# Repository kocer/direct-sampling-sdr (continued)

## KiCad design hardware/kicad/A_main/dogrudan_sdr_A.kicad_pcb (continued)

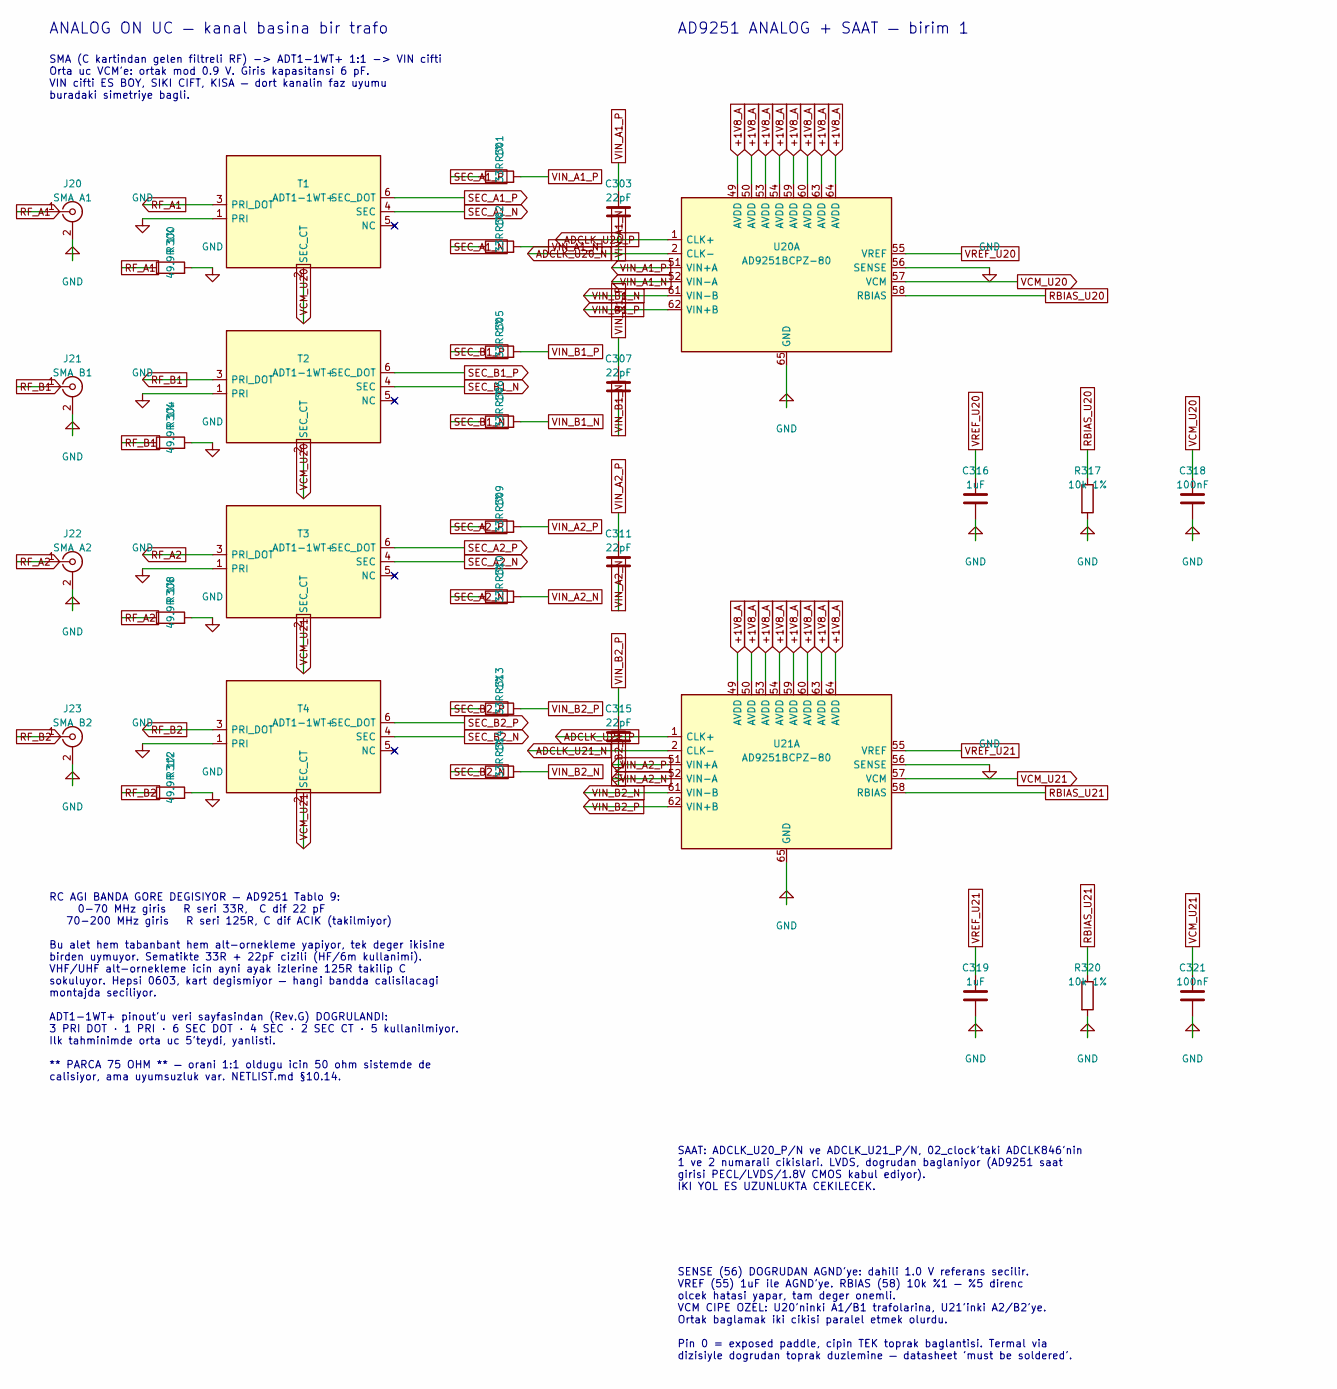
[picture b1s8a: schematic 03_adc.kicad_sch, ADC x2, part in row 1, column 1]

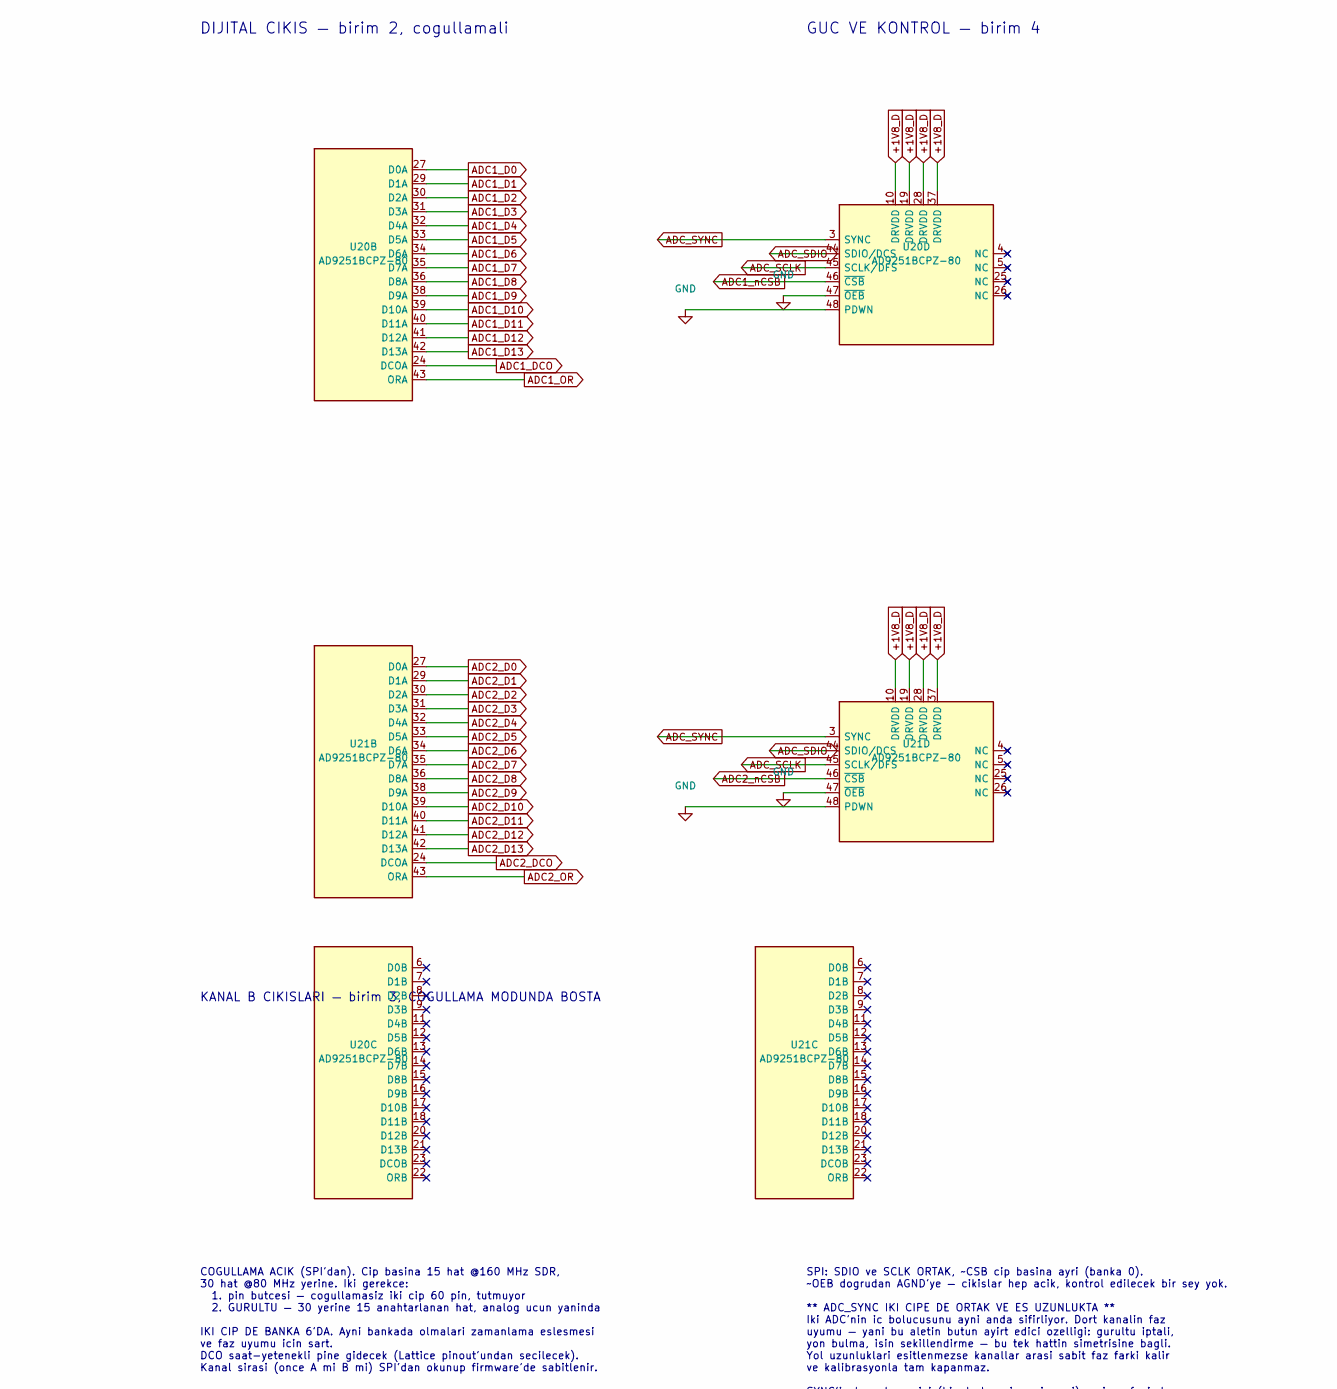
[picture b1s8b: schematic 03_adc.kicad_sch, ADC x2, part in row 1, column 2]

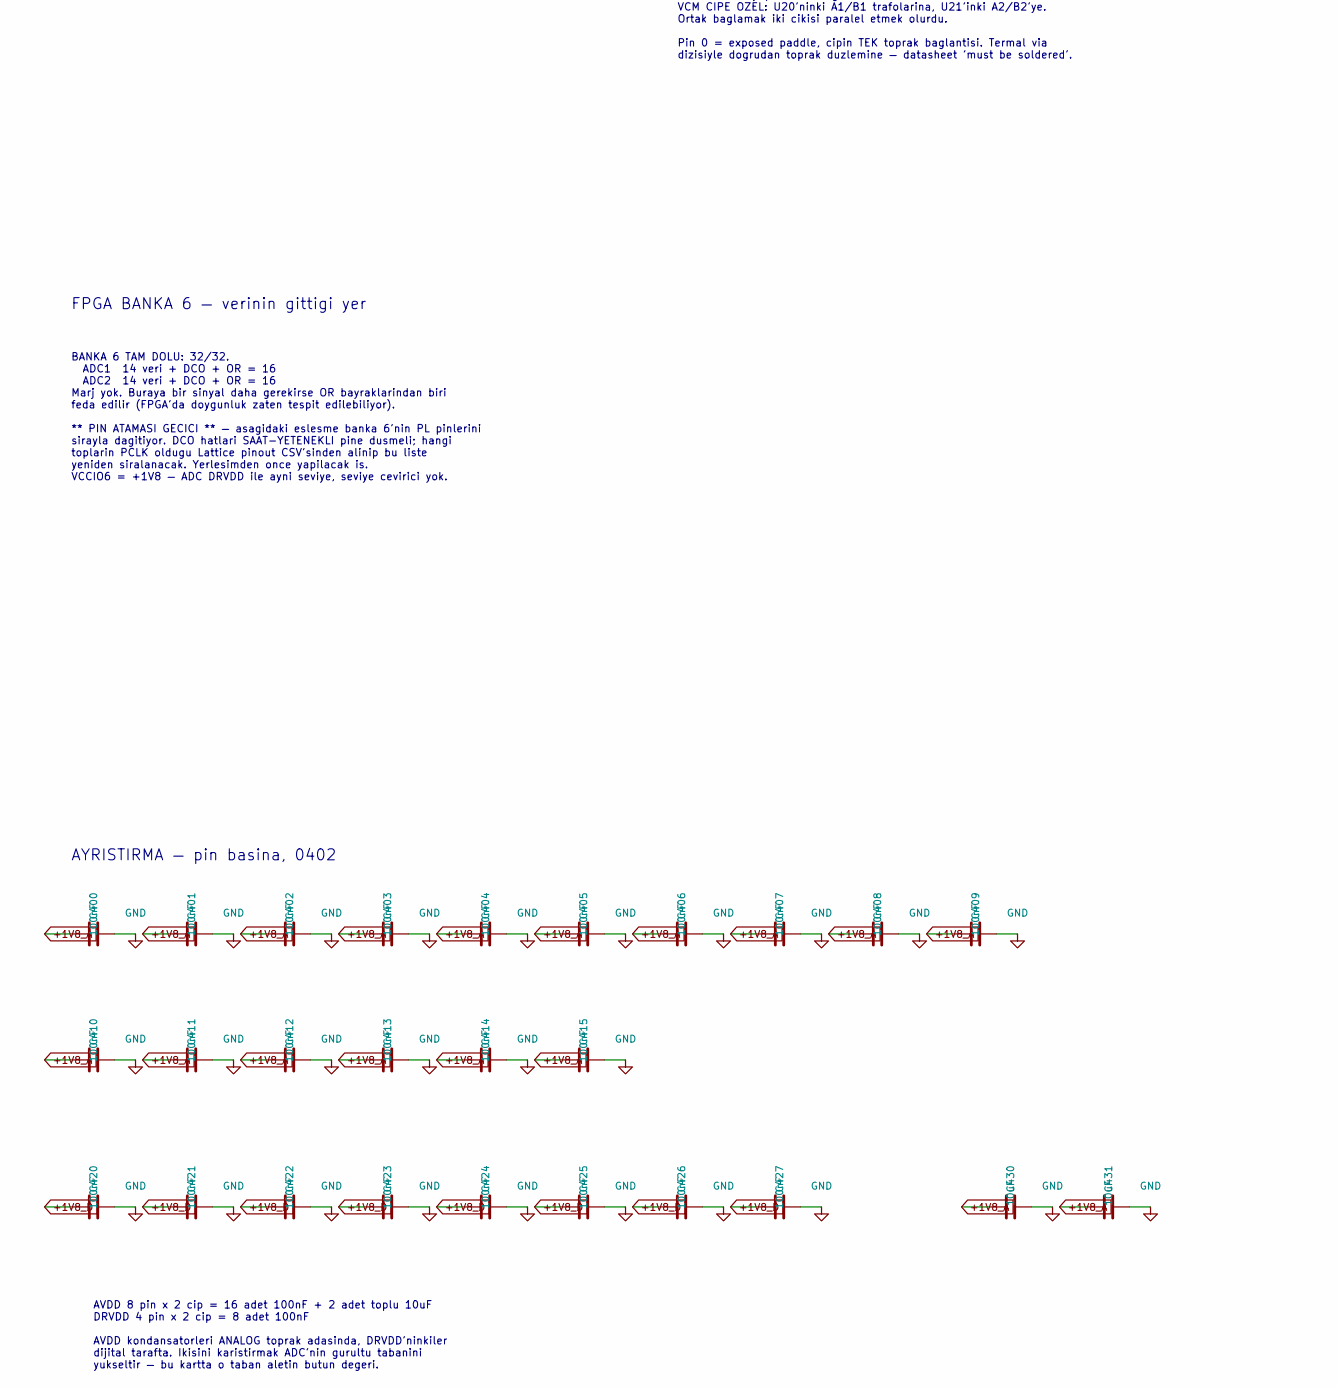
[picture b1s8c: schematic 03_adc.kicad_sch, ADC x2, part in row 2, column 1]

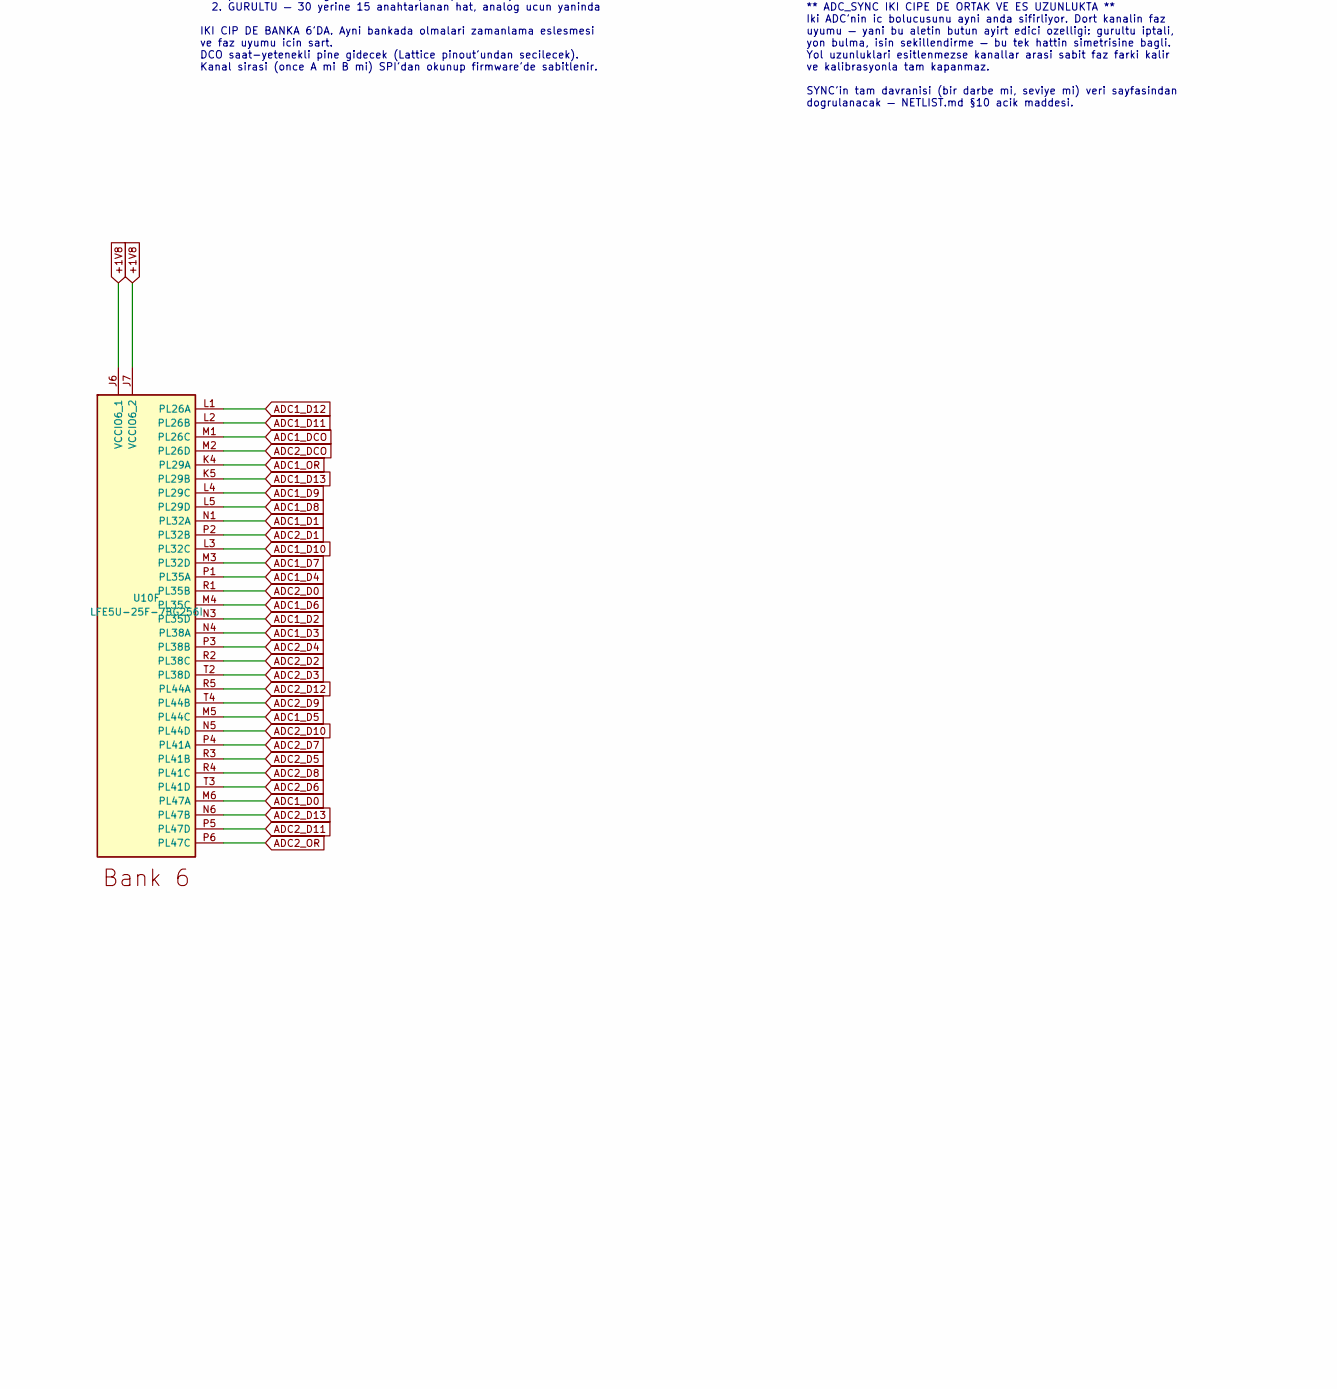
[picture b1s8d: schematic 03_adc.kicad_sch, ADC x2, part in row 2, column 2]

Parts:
C303, C307, C311, C315: 22pF; C_0603_1608Metric
C316, C319: 1uF; C_0603_1608Metric
C318, C321: 100nF; C_0603_1608Metric
C400, C401, C402, C403, C404, C405, C406, C407, C408, C409, C410, C411, C412, C413, C414, C415, C420, C421, C422, C423, C424, C425, C426, C427: 100nF; C_0402_1005Metric
C430, C431: 10uF; C_0402_1005Metric
J20: SMA A1; SMA_Amphenol_132289_EdgeMount
J21: SMA B1; SMA_Amphenol_132289_EdgeMount
J22: SMA A2; SMA_Amphenol_132289_EdgeMount
J23: SMA B2; SMA_Amphenol_132289_EdgeMount
R300, R304, R308, R312: 49.9R 1%; R_0603_1608Metric
R301, R302, R305, R306, R309, R310, R313, R314: 33R 1%; R_0603_1608Metric
R317, R320: 10k 1%; R_0603_1608Metric
T1, T2, T3, T4: ADT1-1WT+; Mini-Circuits_CD542_H2.84mm
U10: LFE5U-25F-7BG256I; BGA-256_14.0x14.0mm_Layout16x16_P0.8mm_Ball0.45mm_Pad0.32mm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
U20, U21: AD9251BCPZ-80; QFN-64-1EP_9x9mm_P0.5mm_EP4.7x4.7mm

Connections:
+1V8: U10.J6 (VCCIO6_1), U10.J7 (VCCIO6_2); also elsewhere on the board
+1V8_D: C420.1, C421.1, C422.1, C423.1, C424.1, C425.1, C426.1, C427.1, U20.10 (DRVDD), U20.19 (DRVDD), U20.28 (DRVDD), U20.37 (DRVDD), U21.10 (DRVDD), U21.19 (DRVDD), U21.28 (DRVDD), U21.37 (DRVDD); also elsewhere on the board
ADC1_D0: U10.M6 (PL47A), U20.27 (D0A)
ADC1_D1: U10.N1 (PL32A), U20.29 (D1A)
ADC1_D2: U10.N3 (PL35D), U20.30 (D2A)
ADC1_D3: U10.N4 (PL38A), U20.31 (D3A)
ADC1_D4: U10.P1 (PL35A), U20.32 (D4A)
ADC1_D5: U10.M5 (PL44C), U20.33 (D5A)
ADC1_D6: U10.M4 (PL35C), U20.34 (D6A)
ADC1_D7: U10.M3 (PL32D), U20.35 (D7A)
ADC1_D8: U10.L5 (PL29D), U20.36 (D8A)
ADC1_D9: U10.L4 (PL29C), U20.38 (D9A)
ADC1_D10: U10.L3 (PL32C), U20.39 (D10A)
ADC1_D11: U10.L2 (PL26B), U20.40 (D11A)
ADC1_D12: U10.L1 (PL26A), U20.41 (D12A)
ADC1_D13: U10.K5 (PL29B), U20.42 (D13A)
ADC1_DCO: U10.M1 (PL26C), U20.24 (DCOA)
ADC1_OR: U10.K4 (PL29A), U20.43 (ORA)
ADC1_nCSB: U20.46 (~CSB); also elsewhere on the board
ADC2_D0: U10.R1 (PL35B), U21.27 (D0A)
ADC2_D1: U10.P2 (PL32B), U21.29 (D1A)
ADC2_D2: U10.R2 (PL38C), U21.30 (D2A)
ADC2_D3: U10.T2 (PL38D), U21.31 (D3A)
ADC2_D4: U10.P3 (PL38B), U21.32 (D4A)
ADC2_D5: U10.R3 (PL41B), U21.33 (D5A)
ADC2_D6: U10.T3 (PL41D), U21.34 (D6A)
ADC2_D7: U10.P4 (PL41A), U21.35 (D7A)
ADC2_D8: U10.R4 (PL41C), U21.36 (D8A)
ADC2_D9: U10.T4 (PL44B), U21.38 (D9A)
ADC2_D10: U10.N5 (PL44D), U21.39 (D10A)
ADC2_D11: U10.P5 (PL47D), U21.40 (D11A)
ADC2_D12: U10.R5 (PL44A), U21.41 (D12A)
ADC2_D13: U10.N6 (PL47B), U21.42 (D13A)
ADC2_DCO: U10.M2 (PL26D), U21.24 (DCOA)
ADC2_OR: U10.P6 (PL47C), U21.43 (ORA)
ADC2_nCSB: U21.46 (~CSB); also elsewhere on the board
ADCLK_U20_N: U20.2 (CLK-); also elsewhere on the board
ADCLK_U20_P: U20.1 (CLK+); also elsewhere on the board
ADCLK_U21_N: U21.2 (CLK-); also elsewhere on the board
ADCLK_U21_P: U21.1 (CLK+); also elsewhere on the board
ADC_SCLK: U20.45 (SCLK/DFS), U21.45 (SCLK/DFS); also elsewhere on the board
ADC_SDIO: U20.44 (SDIO/DCS), U21.44 (SDIO/DCS); also elsewhere on the board
ADC_SYNC: U20.3 (SYNC), U21.3 (SYNC); also elsewhere on the board
RBIAS_U20: R317.1, U20.58 (RBIAS)
RBIAS_U21: R320.1, U21.58 (RBIAS)
RF_A1: J20.1 (In), R300.1, T1.3 (PRI_DOT)
RF_A2: J22.1 (In), R308.1, T3.3 (PRI_DOT)
RF_B1: J21.1 (In), R304.1, T2.3 (PRI_DOT)
RF_B2: J23.1 (In), R312.1, T4.3 (PRI_DOT)
SEC_A1_N: R302.1, T1.4 (SEC)
SEC_A1_P: R301.1, T1.6 (SEC_DOT)
SEC_A2_N: R310.1, T3.4 (SEC)
SEC_A2_P: R309.1, T3.6 (SEC_DOT)
SEC_B1_N: R306.1, T2.4 (SEC)
SEC_B1_P: R305.1, T2.6 (SEC_DOT)
SEC_B2_N: R314.1, T4.4 (SEC)
SEC_B2_P: R313.1, T4.6 (SEC_DOT)
VCM_U20: C318.1, T1.2 (SEC_CT), T2.2 (SEC_CT), U20.57 (VCM)
VCM_U21: C321.1, T3.2 (SEC_CT), T4.2 (SEC_CT), U21.57 (VCM)
VIN_A1_N: C303.2, R302.2, U20.52 (VIN-A)
VIN_A1_P: C303.1, R301.2, U20.51 (VIN+A)
VIN_A2_N: C311.2, R310.2, U21.52 (VIN-A)
VIN_A2_P: C311.1, R309.2, U21.51 (VIN+A)
VIN_B1_N: C307.2, R306.2, U20.61 (VIN-B)
VIN_B1_P: C307.1, R305.2, U20.62 (VIN+B)
VIN_B2_N: C315.2, R314.2, U21.61 (VIN-B)
VIN_B2_P: C315.1, R313.2, U21.62 (VIN+B)
VREF_U20: C316.1, U20.55 (VREF)
VREF_U21: C319.1, U21.55 (VREF)

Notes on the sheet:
BANKA 6 TAM DOLU: 32/32. ADC1 14 veri + DCO + OR = 16 ADC2 14 veri + DCO + OR = 16 Marj yok. Buraya bir sinyal daha gerekirse OR bayraklarindan biri feda edilir (FPGA'da doygunluk zaten tespit edilebiliyor). ** PIN ATAMASI GECICI ** — asagidaki eslesme banka 6'nin PL pinlerini sirayla dagitiyor. DC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
GUC VE KONTROL — birim 4
RC AGI BANDA GORE DEGISIYOR — AD9251 Tablo 9: 0-70 MHz giris R seri 33R, C dif 22 pF 70-200 MHz giris R seri 125R, C dif ACIK (takilmiyor) Bu alet hem tabanbant hem alt-ornekleme yapiyor, tek deger ikisine birden uymuyor. Sematikte 33R + 22pF cizili (HF/6m kullanimi). VHF/UHF alt-ornekleme icin ayn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
AD9251 ANALOG + SAAT — birim 1
ANALOG ON UC — kanal basina bir trafo
KANAL B CIKISLARI — birim 3, COGULLAMA MODUNDA BOSTA
COGULLAMA ACIK (SPI'dan). Cip basina 15 hat @160 MHz SDR, 30 hat @80 MHz yerine. Iki gerekce: 1. pin butcesi — cogullamasiz iki cip 60 pin, tutmuyor 2. GURULTU — 30 yerine 15 anahtarlanan hat, analog ucun yaninda IKI CIP DE BANKA 6'DA. Ayni bankada olmalari zamanlama eslesmesi ve faz uyumu icin sar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
AVDD 8 pin x 2 cip = 16 adet 100nF + 2 adet toplu 10uF DRVDD 4 pin x 2 cip = 8 adet 100nF AVDD kondansatorleri ANALOG toprak adasinda, DRVDD'ninkiler dijital tarafta. Ikisini karistirmak ADC'nin gurultu tabanini yukseltir — bu kartta o taban aletin butun degeri.
SPI: SDIO ve SCLK ORTAK, ~CSB cip basina ayri (banka 0). ~OEB dogrudan AGND'ye — cikislar hep acik, kontrol edilecek bir sey yok. ** ADC_SYNC IKI CIPE DE ORTAK VE ES UZUNLUKTA ** Iki ADC'nin ic bolucusunu ayni anda sifirliyor. Dort kanalin faz uyumu — yani bu aletin butun ayirt edici ozelligi: guru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
SAAT: ADCLK_U20_P/N ve ADCLK_U21_P/N, 02_clock'taki ADCLK846'nin 1 ve 2 numarali cikislari. LVDS, dogrudan baglaniyor (AD9251 saat girisi PECL/LVDS/1.8V CMOS kabul ediyor). IKI YOL ES UZUNLUKTA CEKILECEK.
SMA (C kartindan gelen filtreli RF) -> ADT1-1WT+ 1:1 -> VIN cifti Orta uc VCM'e: ortak mod 0.9 V. Giris kapasitansi 6 pF. VIN cifti ES BOY, SIKI CIFT, KISA — dort kanalin faz uyumu buradaki simetriye bagli.
FPGA BANKA 6 — verinin gittigi yer
DIJITAL CIKIS — birim 2, cogullamali
SENSE (56) DOGRUDAN AGND'ye: dahili 1.0 V referans secilir. VREF (55) 1uF ile AGND'ye. RBIAS (58) 10k %1 — %5 direnc olcek hatasi yapar, tam deger onemli. VCM CIPE OZEL: U20'ninki A1/B1 trafolarina, U21'inki A2/B2'ye. Ortak baglamak iki cikisi paralel etmek olurdu. Pin 0 = exposed paddle, cipin TEK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
AYRISTIRMA — pin basina, 0402

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
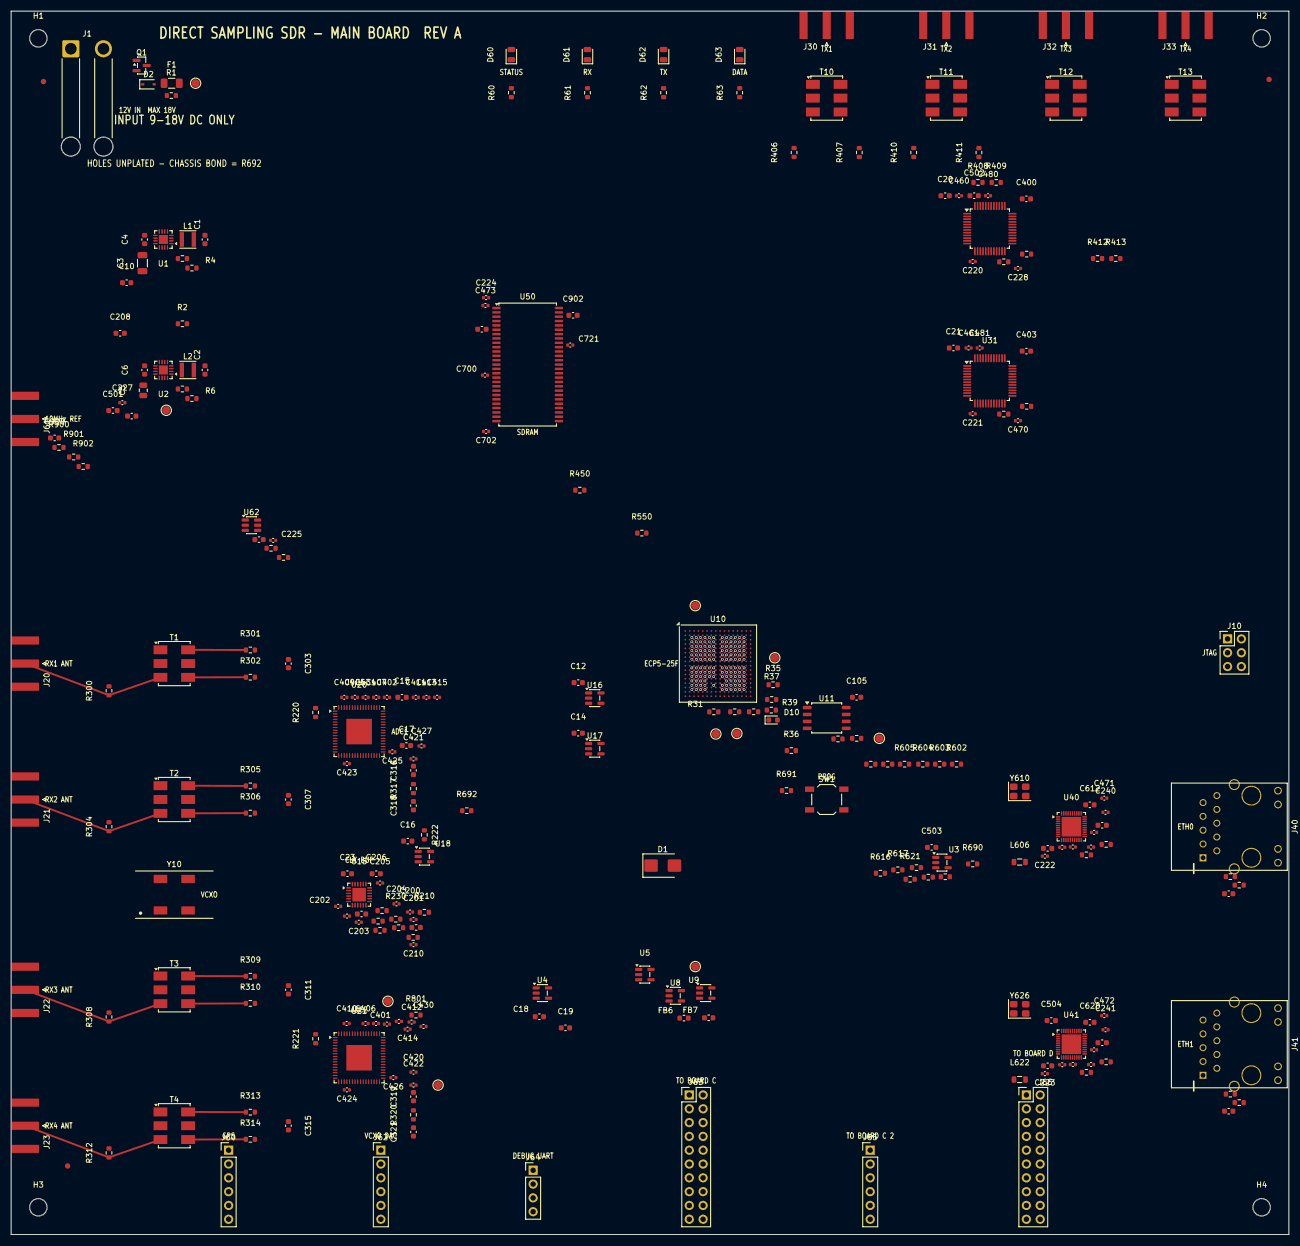
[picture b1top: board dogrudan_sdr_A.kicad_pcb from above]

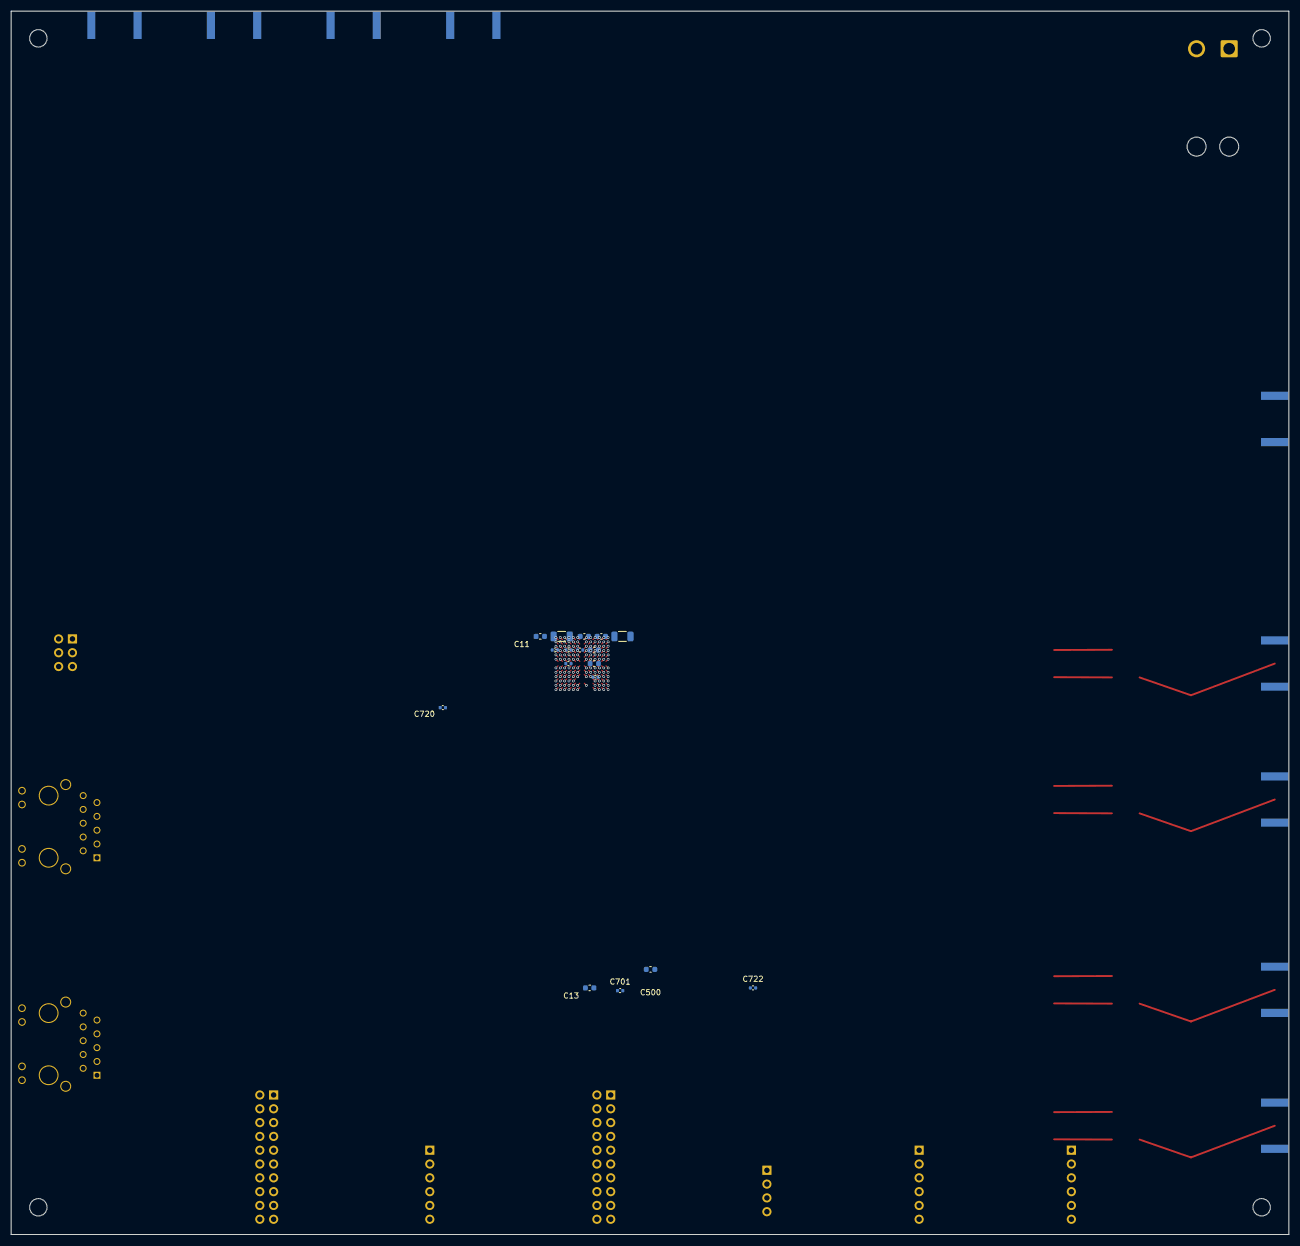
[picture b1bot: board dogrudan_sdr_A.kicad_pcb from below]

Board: 6 copper layers, 235.0 x 225.0 mm, 297 parts (17 on the bottom side), 336 nets.

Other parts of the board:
FID1, FID2, FID3: ​FID; Fiducial_1mm_Mask2mm
H1, H2, H3, H4: MountingHole_3.2mm_M3
TP1: ​+1V1; TestPoint_Pad_D1.5mm
TP2: ​+1V8_A; TestPoint_Pad_D1.5mm
TP3: ​+1V8_D; TestPoint_Pad_D1.5mm
TP4: ​+2V5; TestPoint_Pad_D1.5mm
TP5: ​+3V3; TestPoint_Pad_D1.5mm
TP6: ​VIN_PROT; TestPoint_Pad_D1.5mm
TP7: ​FPGA_CLK80; TestPoint_Pad_D1.5mm
TP8: ​DONE; TestPoint_Pad_D1.5mm
TP9: ​nINIT; TestPoint_Pad_D1.5mm
TP10: ​REF10_IN; TestPoint_Pad_D1.5mm

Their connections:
+1V8_D: TP3.1; also elsewhere on the board
DONE: TP8.1; also elsewhere on the board
FPGA_CLK80: TP7.1; also elsewhere on the board
REF10_IN: TP10.1; also elsewhere on the board
nINIT: TP9.1; also elsewhere on the board

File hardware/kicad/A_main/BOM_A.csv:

Comment,Designator,Footprint,LCSC
0R,"R450,R691,R692,R801",Resistor_SMD:R_0603_1608Metric,C21189
1.5k,R690,Resistor_SMD:R_0603_1608Metric,C4310
1.92k 1%,"R401,R402,R404,R405",Resistor_SMD:R_0603_1608Metric,C23025
100R,"R207,R209,R211,R220,R221,R222,R230",Resistor_SMD:R_0603_1608Metric,C25076
100k,"R1,R2,R3",Resistor_SMD:R_0603_1608Metric,C25741
100nF,"C200,C201,C202,C203,C204,C205,C210,C211,C220,C221,C222,C223,C224,C225,C226,C227,C228,C240,C241,C242,C243,C400,C401,C402,C403,C404,C405,C406,C407,C408,C409,C410,C411,C412,C413,C414,C415,C420,C421,C422,C423,C424,C425,C426,C427,C460,C461,C470,C471,C472,C473,C700,C701,C702,C703,C704,C705,C706,C707,C720,C721,C722,C723,C724,C725,C726,C727",Capacitor_SMD:C_0402_1005Metric,C1525
100nF,"C19,C200,C202,C203,C204,C205,C208,C21,C210,C211,C212,C318,C321,C4,C400,C403,C500,C501,C502,C503,C504,C505,C6,C900,C901,C902",Capacitor_SMD:C_0603_1608Metric,C1525
100nF 2kV,"C615,C631",Capacitor_SMD:C_0603_1608Metric,C336276
10k,"R20,R21,R36,R37,R38,R5,R609,R625,R901,R902,R903,R904",Resistor_SMD:R_0603_1608Metric,C25744
10k 1%,"R317,R320",Resistor_SMD:R_0603_1608Metric,C25744
10uF,"C430,C431,C480,C481",Capacitor_SMD:C_0402_1005Metric,C15850
10uF,"C101,C102,C103,C105,C18,C20,C201,C206,C506",Capacitor_SMD:C_0603_1608Metric,C15850
10uF,C5,Capacitor_SMD:C_0805_2012Metric,C15850
10uF,C3,Capacitor_SMD:C_1206_3216Metric,C15850
10uF X5R,"C607,C623",Capacitor_SMD:C_0603_1608Metric,C15850
12V,D2,Diode_SMD:D_SOD-323,C8062
18pF,"C611,C612,C627,C628",Capacitor_SMD:C_0603_1608Metric,C1584
1k,"R212,R213,R39,R60,R600,R601,R602,R603,R604,R605,R61,R616,R617,R618,R619,R62,R620,R621,R63",Resistor_SMD:R_0603_1608Metric,C21190
1uF,"C10,C11,C12,C13,C14,C15,C16,C17,C22,C23,C316,C319",Capacitor_SMD:C_0603_1608Metric,C52923
2.2k 1%,"R608,R624",Resistor_SMD:R_0603_1608Metric,C4190
2.2uH,"L1,L2",Inductor_SMD:L_Taiyo-Yuden_NR-30xx,C1017
220R,R210,Resistor_SMD:R_0603_1608Metric,C25091
22R,R550,Resistor_SMD:R_0603_1608Metric,C25092
22pF,"C303,C307,C311,C315",Capacitor_SMD:C_0603_1608Metric,C1554
22uF,"C1,C2",Capacitor_SMD:C_0603_1608Metric,C45783
25MHz CL12pF,"Y610,Y626",Crystal:Crystal_SMD_3225-4Pin_3.2x2.5mm,C9006
26.7k,R6,Resistor_SMD:R_0603_1608Metric,C25765
2A,F1,Fuse:Fuse_1206_3216Metric,C371166
32k,R4,Resistor_SMD:R_0603_1608Metric,C25768
330R,"R613,R614,R629,R630",Resistor_SMD:R_0603_1608Metric,C25104
33R 1%,"R301,R302,R305,R306,R309,R310,R313,R314",Resistor_SMD:R_0603_1608Metric,C25105
4.7k,R32,Resistor_SMD:R_0603_1608Metric,C23162
4.7uH,"L606,L622",Inductor_SMD:L_0805_2012Metric,C1018
470R,"R31,R35",Resistor_SMD:R_0603_1608Metric,C23179
47uF,"C100,C104",Capacitor_SMD:C_1206_3216Metric,C46653
49.9R 1%,"R300,R304,R308,R312",Resistor_SMD:R_0603_1608Metric,C25107
50R 1%,"R406,R407,R408,R409,R410,R411,R412,R413,R900",Resistor_SMD:R_0603_1608Metric,C22775
ABLNO-V-80.000MHZ,Y10,dogrudan-sdr:Oscillator_Abracon_ABLNO_4pad_14.3x8.7mm,C5378891
AD9251BCPZ-80,"U20,U21",Package_DFN_QFN:QFN-64-1EP_9x9mm_P0.5mm_EP4.7x4.7mm,C653380
AD9767ASTZ,"U30,U31",Package_QFP:LQFP-48_7x7mm_P0.5mm,C653820
ADCLK846BCPZ,U15,Package_DFN_QFN:HVQFN-24-1EP_4x4mm_P0.5mm_EP2.5x2.5mm,C578957
ADP150-1.8,"U4,U5,U9",Package_TO_SOT_SMD:TSOT-23-5,C141959
ADP150-2.5,U8,Package_TO_SOT_SMD:TSOT-23-5,C144257
ADT1-1WT+,"T1,T10,T11,T12,T13,T2,T3,T4",RF_Mini-Circuits:Mini-Circuits_CD542_H2.84mm,C6835853
C kartina,J63,Connector_PinHeader_2.54mm:PinHeader_2x10_P2.54mm_Vertical,EL
C kartina #2,J65,Connector_PinHeader_2.54mm:PinHeader_1x06_P2.54mm_Vertical,EL
D kartina,J66,Connector_PinHeader_2.54mm:PinHeader_2x10_P2.54mm_Vertical,EL
DAC modul,J62,Connector_PinHeader_2.54mm:PinHeader_1x06_P2.54mm_Vertical,EL
DMP3098L,Q1,Package_TO_SOT_SMD:SOT-23,C155039
GPS modul,J60,Connector_PinHeader_2.54mm:PinHeader_1x06_P2.54mm_Vertical,EL
HR911130A,"J40,J41",dogrudan-sdr:RJ45_Hanrun_HR911130A,C54408
JTAG 2x3,J10,Connector_PinHeader_2.54mm:PinHeader_2x03_P2.54mm_Vertical,EL
LFE5U-25F-7BG256I,U10,Package_BGA:BGA-256_14.0x14.0mm_Layout16x16_P0.8mm_Ball0.45mm_Pad0.32mm_NSMD,C1550762
PROG,SW1,Button_Switch_SMD:SW_SPST_TL3342,C318884
RTL8211FI-CG,"U40,U41",Package_DFN_QFN:QFN-40-1EP_5x5mm_P0.4mm_EP3.6x3.6mm,C717681
SMA 10MHz ref,J61,Connector_Coaxial:SMA_Amphenol_132289_EdgeMount,C496550
SMA A1,J20,Connector_Coaxial:SMA_Amphenol_132289_EdgeMount,C496550
SMA A2,J22,Connector_Coaxial:SMA_Amphenol_132289_EdgeMount,C496550
SMA B1,J21,Connector_Coaxial:SMA_Amphenol_132289_EdgeMount,C496550
SMA B2,J23,Connector_Coaxial:SMA_Amphenol_132289_EdgeMount,C496550
SMA TX1,J30,Connector_Coaxial:SMA_Amphenol_132289_EdgeMount,C496550
SMA TX2,J31,Connector_Coaxial:SMA_Amphenol_132289_EdgeMount,C496550
SMA TX3,J32,Connector_Coaxial:SMA_Amphenol_132289_EdgeMount,C496550
SMA TX4,J33,Connector_Coaxial:SMA_Amphenol_132289_EdgeMount,C496550
SMBJ20A,D1,Diode_SMD:D_SMB,C364296
SN65LVDS2DBVR,"U16,U17,U18",Package_TO_SOT_SMD:SOT-23-5,C38204
TLV3501AIDBVR,U62,Package_TO_SOT_SMD:SOT-23-6,C193413
TPS62130,"U1,U2",Package_DFN_QFN:VQFN-16-1EP_3x3mm_P0.5mm_EP1.68x1.68mm,C337502
TPS7A2018,U3,Package_TO_SOT_SMD:SOT-23-5,C963430
UART 3.3V,J64,Connector_PinHeader_2.54mm:PinHeader_1x04_P2.54mm_Vertical,EL
W25Q128JVSIQ,U11,Package_SO:SOIC-8_5.3x5.3mm_P1.27mm,C97521
W9825G6KH-6I,U50,Package_SO:TSOP-II-54_22.2x10.16mm_P0.8mm,C97572
XT60,J1,Connector_Wire:SolderWire-1.5sqmm_1x02_P6mm_D1.7mm_OD3mm_Relief,C98732
ferrit 600R,"FB10,FB6,FB7",Inductor_SMD:L_0603_1608Metric,C1015
kirmizi,D62,LED_SMD:LED_0805_2012Metric,C84256
mavi,D61,LED_SMD:LED_0805_2012Metric,C2293
sari,D63,LED_SMD:LED_0805_2012Metric,C2296
yesil,D10,LED_SMD:LED_0603_1608Metric,C72043
yesil,D60,LED_SMD:LED_0805_2012Metric,C72043
